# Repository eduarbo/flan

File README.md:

# Flan

**Homemade, like a good flan.** An open-source wireless split keyboard in four sizes, with interchangeable cases, magnetic display frames, 31 themes and your own keycap colors.

**[flankbd.com →](https://flankbd.com/)** · **[Explore and customize in 3D →](https://flankbd.com/explore/)** · **[Parts and buying links →](docs/parts.md)** · **[Order PCBs →](docs/electronics.md#order-the-two-pcbs)** · **[Build guide →](docs/build.md)** · **[Edit in FreeCAD →](docs/freecad.md)**

| [Home page](https://flankbd.com/) | [3D explorer](https://flankbd.com/explore/) |
|---|---|
|  |  |

**[Four sizes](docs/variants.md)** — Flan36 (3 × 5 + 3 per half) is the reference. Flan42 adds the outer pinky column, Flan46 a number row and Flan54 both. Every size keeps the thumbs and the bay, and has routed PCBs, six silkscreen editions, the four case styles and ZMK firmware. Pick one in the explorer under **Design → Size**.

**[Silkscreen editions](docs/electronics.md#editions)** — Asanoha, Kikkō, Sayagata, Seigaiha, Meandro and Vías: six all-over back patterns around the Flan signature, one Gerber package each. Preview them with JLCPCB's seven solder-mask colors under **Design → PCB**, which links the matching ZIPs.

**[Themes and print kits](docs/themes-printing.md)** — Thirty-one coordinated themes, personal keycap palettes, linked rim/frame colors and selected STL/3MF parts.

**[Lower, level stack](docs/level-stack.md)** — The frame and removable switch-covering shell reach 14.50 mm; the glass sits 0.20 mm below them. The display uses its supplied 5 mm socket + 2 mm header; physical assembly remains to be tested.

**[Case styles](docs/cases.md)** — Level, Solid, Color rim and Terrace; actual meshes in the explorer.

**[Using the explorer](docs/viewer.md)** — Design, Parts and Build beside the model (Build lists every part, PCB, print file and firmware for your design), a phone sheet with the home page's tabs, share links that open your exact keyboard, English and Spanish. [Port refinement and verification](docs/reviews/interaction-refinement.md) documents the restored frame wall around USB and power access, including the retained cable and switch clearances.

Flan is a low-profile wireless split keyboard in development by [Eduardo Ruiz](https://github.com/eduarbo). Its original CAD is designed by Eduardo; Flan36 has five columns and three thumb keys per half.

- **KLP Lamé choices:** all 38 Choc-stem variants catalogued; 28 qualify in at least one position. The explorer checks complete combinations and exports a configuration for FreeCAD.
- **Magnetic frames:** six Ø2 × 3 mm base magnets pair with six Ø2 × 4 mm frame magnets from existing stock; [polarity and assembly](docs/build.md#magnetic-frame-and-service). Talavera (default), Game Boy, SNES, 2000s Phone, iPod and Hanafuda. Up to four solid colors in flush inlays, with matching rim and key palettes.
- **Keycap colors:** paint all keys, rows, columns or individual keys; save and share your own palettes.
- **Free tools:** KiCad for electronics, FreeCAD for the case, StepUp for exchange. Editable source, STEP/STL, offline explorer and GLB included.
- **Intended hardware:** Choc v1 hot-swap, two nice!nano controllers and two nice!view displays. One display remains the fallback.

**Status: first Flan36 parts ordered; physical qualification pending.** Both Flan36 PCBs pass DRC, schematic parity and ERC with no unconnected items. Three [ZMK firmware builds](docs/firmware.md) cover two displays or a left-only display. [Prototype fabrication files and verification](docs/electronics.md) are included. Exact connectors, printed retention, BLE, charging and measured power still need hardware tests.

**First build:** [Flan36 purchase sequence and test record](docs/first-build.md). **Introducing Flan:** [copy, images and verified claim boundaries](docs/launch.md).

| Level | Solid | Color rim | Terrace |
|---|---|---|---|
|  |  |  |  |

**[Keycaps and frames](docs/customize.md) · [Design](docs/design.md) · [Build](docs/build.md) · [CAD files](docs/cad.md) · [Explorer](docs/viewer.md) · [Progress](docs/progress.md)**

Flan36 is inspired by [Piantor by beekeeb](https://github.com/beekeeb/piantor) and keeps its 36 key positions and angles; the wireless PCBs, case outline, cases, frames and firmware are original. The viewer uses [KLP Lamé by braindefender](https://github.com/braindefender/KLP-Lame-Keycaps). [Credits and licenses](ATTRIBUTION.md). [Contributing](CONTRIBUTING.md).

## Support Flan

Flan is free to build. If it is useful to you, [support it on Ko-fi](https://ko-fi.com/eduarbo): it funds prototypes, test boards and new sizes.

## License, trademark and official kits

Build, modify, share and sell Flan under [GPL-3.0-or-later](LICENSE), with the third-party terms listed in [ATTRIBUTION.md](ATTRIBUTION.md). The license covers the files, not the **Flan** name and logos: products sold under the Flan name or carrying its marks need permission. Official kits come only from Eduardo or licensed sellers. [Trademark policy and official kits →](TRADEMARKS.md)

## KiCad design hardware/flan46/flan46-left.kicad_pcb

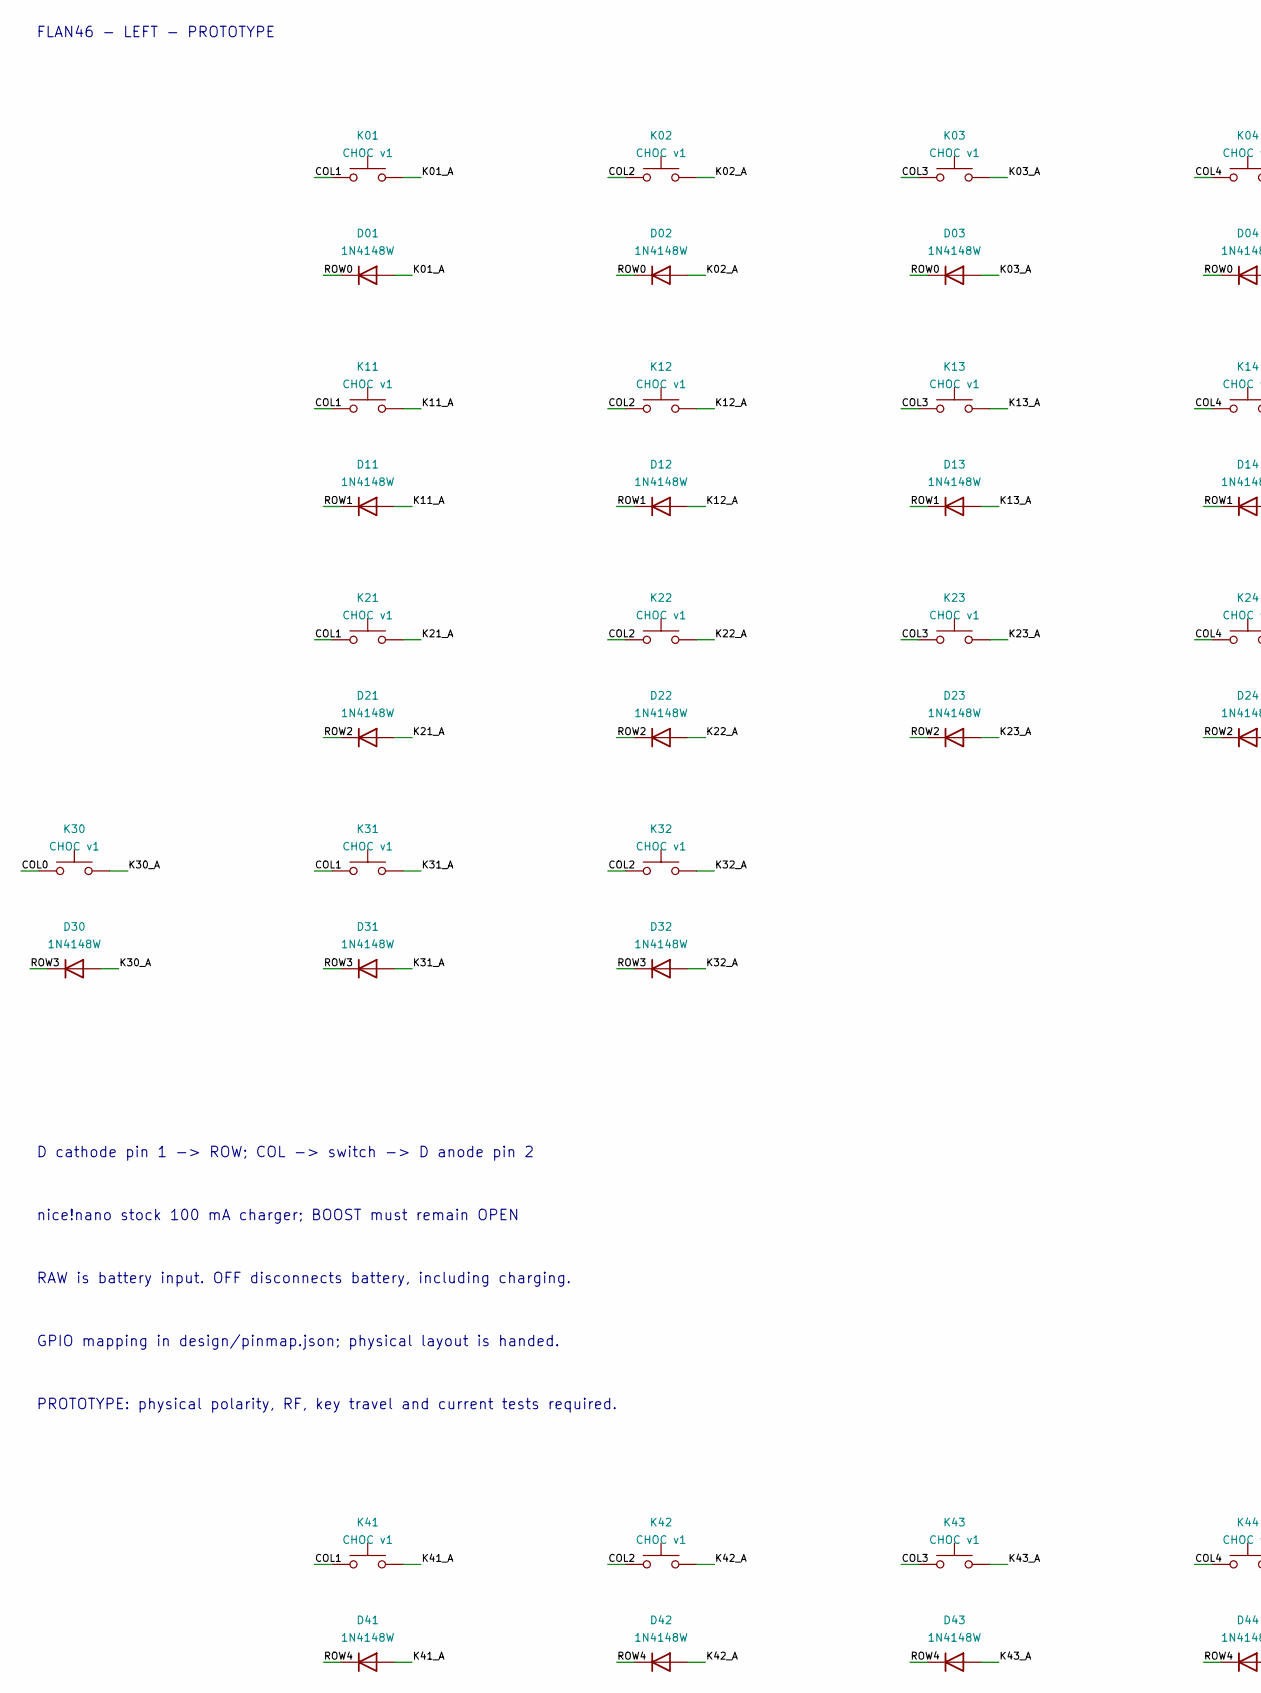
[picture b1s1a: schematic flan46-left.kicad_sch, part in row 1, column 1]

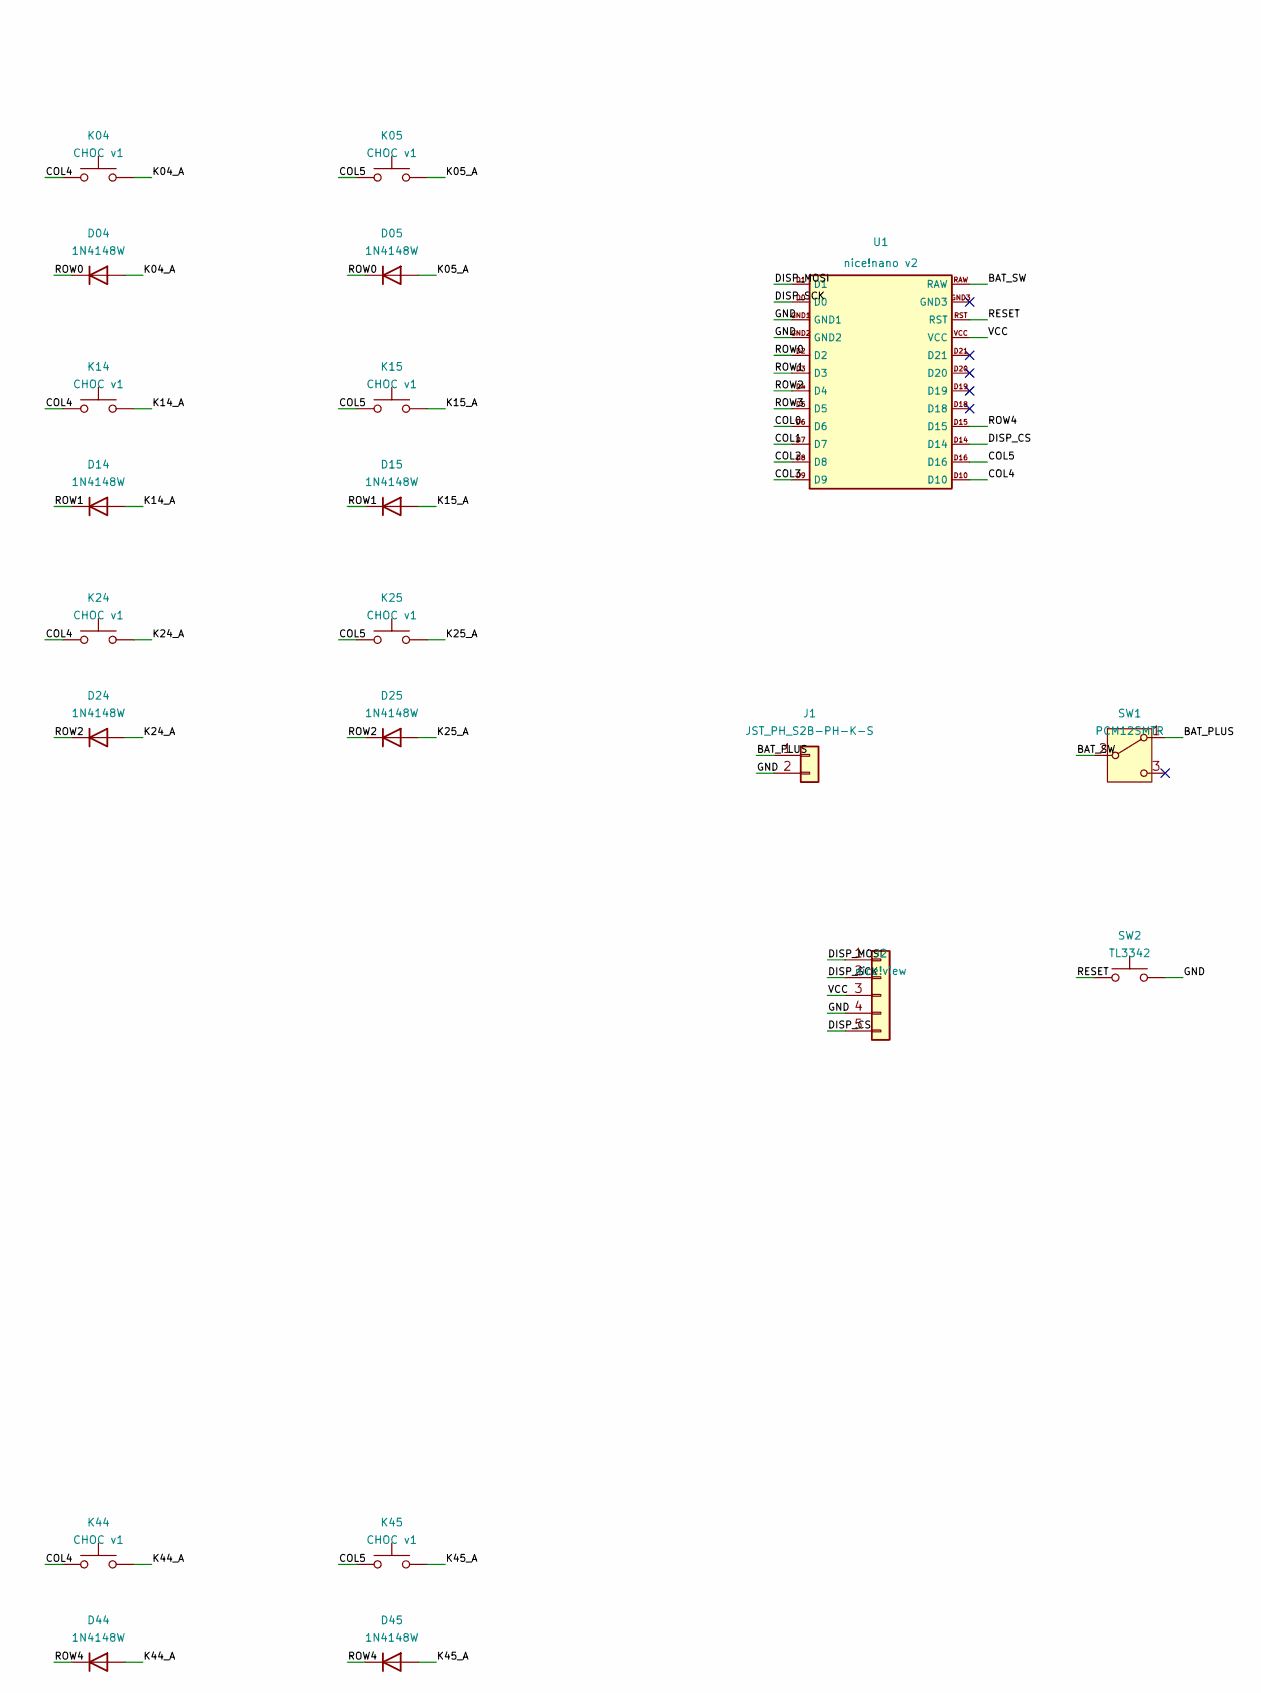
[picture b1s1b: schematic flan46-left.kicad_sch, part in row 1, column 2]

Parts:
D01, D02, D03, D04, D05, D11, D12, D13, D14, D15, D21, D22, D23, D24, D25, D30, D31, D32, D41, D42, D43, D44, D45: 1N4148W; D_SOD-123
J1: JST_PH_S2B-PH-K-S; JST_PH_S2B-PH-K_1x02_P2.00mm_Horizontal
J2: nice!view; nice_view_5pin
K01, K02, K03, K04, K05, K11, K12, K13, K14, K15, K21, K22, K23, K24, K25, K30, K31, K32, K41, K42, K43, K44, K45: CHOC v1; Kailh_socket_PG1350_optional
SW1: PCM12SMTR; SW_SPDT_PCM12
SW2: TL3342; SW_SPST_TL3342
U1: nice!nano v2; nice_nano_v2_standard_edge

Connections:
/BAT_PLUS: J1.1, SW1.1 (A)
/BAT_SW: SW1.2 (B), U1.RAW
/COL0: K30.1, U1.D6
/COL1: K01.1, K11.1, K21.1, K31.1, K41.1, U1.D7
/COL2: K02.1, K12.1, K22.1, K32.1, K42.1, U1.D8
/COL3: K03.1, K13.1, K23.1, K43.1, U1.D9
/COL4: K04.1, K14.1, K24.1, K44.1, U1.D10
/COL5: K05.1, K15.1, K25.1, K45.1, U1.D16
/DISP_CS: J2.5, U1.D14
/DISP_MOSI: J2.1, U1.D1
/DISP_SCK: J2.2, U1.D0
/GND: J1.2, J2.4, SW2.2, U1.GND1, U1.GND2
/K01_A: D01.2 (A), K01.2
/K02_A: D02.2 (A), K02.2
/K03_A: D03.2 (A), K03.2
/K04_A: D04.2 (A), K04.2
/K05_A: D05.2 (A), K05.2
/K11_A: D11.2 (A), K11.2
/K12_A: D12.2 (A), K12.2
/K13_A: D13.2 (A), K13.2
/K14_A: D14.2 (A), K14.2
/K15_A: D15.2 (A), K15.2
/K21_A: D21.2 (A), K21.2
/K22_A: D22.2 (A), K22.2
/K23_A: D23.2 (A), K23.2
/K24_A: D24.2 (A), K24.2
/K25_A: D25.2 (A), K25.2
/K30_A: D30.2 (A), K30.2
/K31_A: D31.2 (A), K31.2
/K32_A: D32.2 (A), K32.2
/K41_A: D41.2 (A), K41.2
/K42_A: D42.2 (A), K42.2
/K43_A: D43.2 (A), K43.2
/K44_A: D44.2 (A), K44.2
/K45_A: D45.2 (A), K45.2
/RESET: SW2.1, U1.RST
/ROW0: D01.1 (K), D02.1 (K), D03.1 (K), D04.1 (K), D05.1 (K), U1.D2
/ROW1: D11.1 (K), D12.1 (K), D13.1 (K), D14.1 (K), D15.1 (K), U1.D3
/ROW2: D21.1 (K), D22.1 (K), D23.1 (K), D24.1 (K), D25.1 (K), U1.D4
/ROW3: D30.1 (K), D31.1 (K), D32.1 (K), U1.D5
/ROW4: D41.1 (K), D42.1 (K), D43.1 (K), D44.1 (K), D45.1 (K), U1.D15
/VCC: J2.3, U1.VCC

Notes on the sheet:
FLAN46 - LEFT - PROTOTYPE
D cathode pin 1 -> ROW; COL -> switch -> D anode pin 2
nice!nano stock 100 mA charger; BOOST must remain OPEN
RAW is battery input. OFF disconnects battery, including charging.
GPIO mapping in design/pinmap.json; physical layout is handed.
PROTOTYPE: physical polarity, RF, key travel and current tests required.

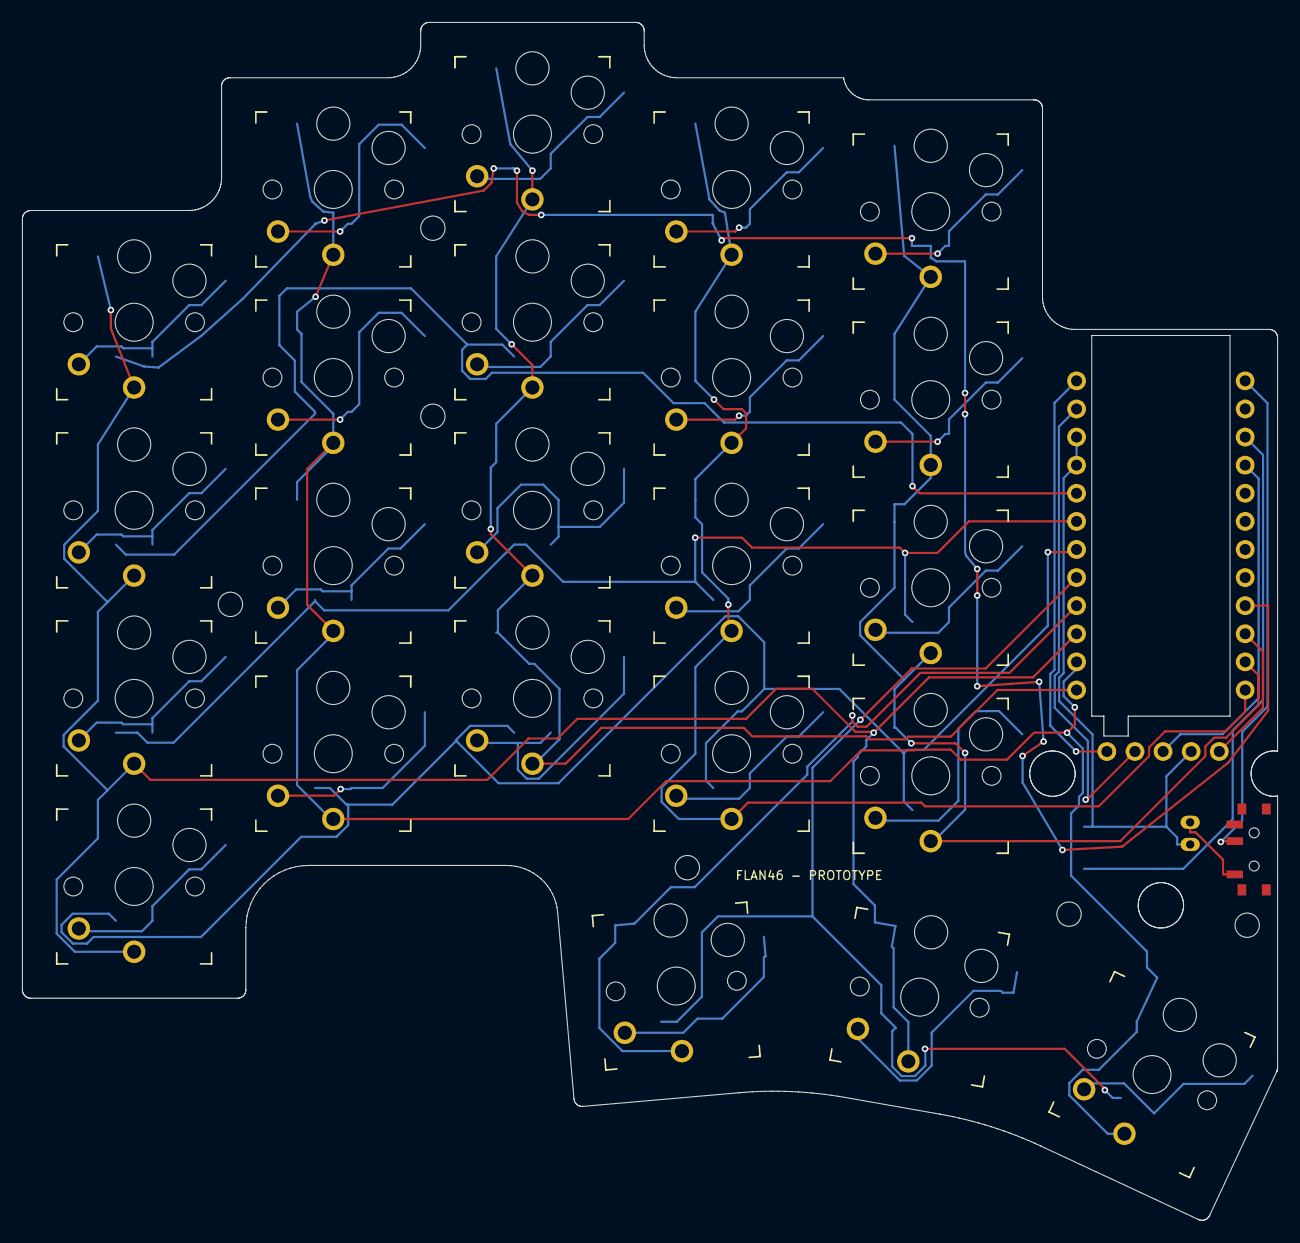
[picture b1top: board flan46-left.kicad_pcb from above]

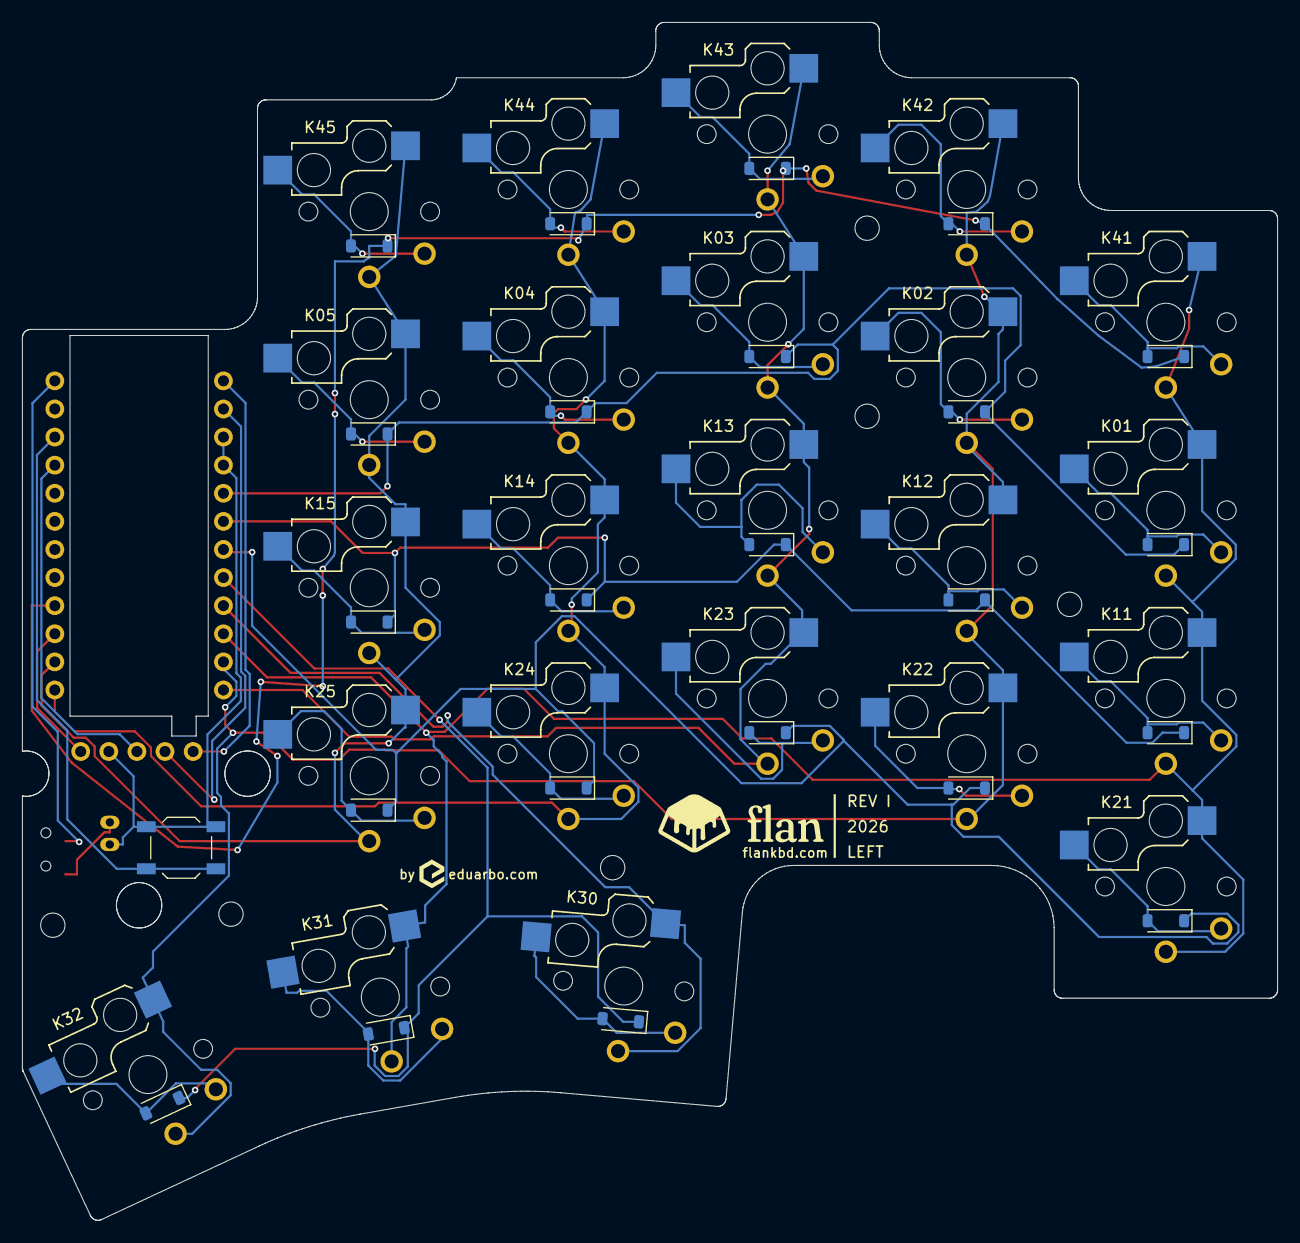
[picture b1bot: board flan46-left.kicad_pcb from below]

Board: 2 copper layers, 113.4 x 108.3 mm, 57 parts (24 on the bottom side), 42 nets.

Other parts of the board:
H1, H2, H3, H4, H5, H7: MountingHole_2.2mm_M2

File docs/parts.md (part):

# Parts and buying guide

**Use [Build in the explorer](https://flankbd.com/explore/) for your configuration’s itemized list, supplier links, quantities and CSV export.** The reference below documents the component selections.

**One complete split keyboard. Quantities cover both halves of Flan36; [other sizes](#quantities-by-size) change only the per-key parts and a few screws.**

This is the selected purchasing BOM for the routed revI prototype, an original design by Eduardo Ruiz. The display uses the connector supplied with nice!view; the controller sockets and pins are specified below. **Physical assembly has not been qualified:** supplied-part tolerances, printed fit, magnetic retention and electrical operation still need the [build checks](build.md).

[Custom PCBs](electronics.md) · [Quantities by size](#quantities-by-size) · [Typeractive shopping list](#typeractive-shopping-list) · [Controllers](#controllers) · [Displays](#displays) · [Switches](#switches-and-hot-swap) · [Battery](#battery) · [Connectors](#removable-connectors) · [Small parts](#small-electrical-parts) · [Printed parts](#printed-parts)

**First prototype:** follow the [Flan36 purchase sequence and test record](first-build.md). [Current supply check](#supply-check-2026-10-20).

**Custom PCBs: 1 left + 1 right**, two layers, 1.6 mm FR4, nominal 1 oz copper. Download the [left fabrication ZIP](https://raw.githubusercontent.com/eduarbo/flan/main/hardware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 and [right fabrication ZIP](https://raw.githubusercontent.com/eduarbo/flan/main/hardware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, then follow the [ordering settings](electronics.md#order-the-two-pcbs). The supplied pin maps differ between halves; neither board is interchangeable with Piantor or the historical placement studies.

## Quantities by size

Everything not listed here is the same for every size: two controllers, two displays, two batteries, two power switches, two reset buttons, the controller connectors, magnets, feet, cable and tape. Packs of switches, sockets and diodes come in tens; each count keeps at least four spares.

| | Flan36 | Flan42 | Flan46 | Flan54 |
|---|:-:|:-:|:-:|:-:|
| Keys per half | 3 × 5 + 3 | 3 × 6 + 3 | 4 × 5 + 3 | 4 × 6 + 3 |
| Choc v1 switches | 36 · **4 packs** | 42 · **5 packs** | 46 · **5 packs** | 54 · **6 packs** |
| Choc hot-swap sockets | 36 · **4 packs** | 42 · **5 packs** | 46 · **5 packs** | 54 · **6 packs** |
| 1N4148W diodes | 36 · **4 packs** | 42 · **5 packs** | 46 · **5 packs** | 54 · **6 packs** |
| KLP Lamé keycaps (printed) | 36 | 42 | 46 | 54 |
| M2 × 6 screws | 6 | 8 | 8 | 12 |
| M2 × 4 screws | 4 | 4 | 4 | 4 |
| Printed spacers/washers | 6 | 8 | 8 | 12 |
| PCB fabrication ZIPs | [left](https://raw.githubusercontent.com/eduarbo/flan/main/hardware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 · [right](https://raw.githubusercontent.com/eduarbo/flan/main/hardware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 | [left](https://raw.githubusercontent.com/eduarbo/flan/main/hardware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 · [right](https://raw.githubusercontent.com/eduarbo/flan/main/hardware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 | [left](https://raw.githubusercontent.com/eduarbo/flan/main/hardware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 · [right](https://raw.githubusercontent.com/eduarbo/flan/main/hardware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 | [left](https://raw.githubusercontent.com/eduarbo/flan/main/hardware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 · [right](https://raw.githubusercontent.com/eduarbo/flan/main/hardware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 |

Every key has its own diode. The added fasteners (H6 on Flan42, H7 on Flan46, H6–H8 on Flan54, per half) copy H1 or H2, so they take M2 × 6 screws and a printed washer. The other sizes are built digitally only; Flan36 is the reference for a first build. [The Flan family](variants.md)

## Typeractive shopping list

| Item | Quantity / store selection | Assembly note |
|---|---|---|
| [nice!nano v2](https://typeractive.xyz/products/nice-nano) | **2 units** | Install with the specified Mill-Max sockets/pins at Z8.20 mm |
| [nice!view](https://typeractive.xyz/products/nice-view) | **2 units** | Use each display's supplied 5-pin socket and header; 7.00 mm board separation |
| [Choc v1 switches](https://typeractive.xyz/products/choc-switches) | **4 packs of 10**; Pro Red baseline | 36 required, 4 spares |
| [Kailh hot-swap sockets](https://typeractive.xyz/products/hotswap-sockets) | **4 packs of 10; select Choc** | Do not select MX |
| [1N4148W SMD diodes](https://typeractive.xyz/products/smd-diodes) | **4 packs of 10** | SOD-123 family; verify supplied marking/footprint |
| [Battery jack](https://typeractive.xyz/products/battery-jack) | **1 pack of 2; white** | JST S2B-PH-K-S side-entry reference; 2 mm nominal footprint |

No additional display connector pack is needed. The selected controller connectors, battery, power switch and reset button are in the following list; the similarly named Typeractive alternatives are not the selected parts.

## DigiKey shopping list

| Item | Quantity | Selection |
|---|---:|---|
| [Adafruit 1570](https://www.digikey.com/en/products/detail/adafruit-industri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 | **2** | Protected 1S 100 mAh LiPo; keep the nice!nano BOOST jumper open |
| [C&K PCM12SMTR](https://www.digikey.com/en/products/detail/c-k/PCM12SMTR/1640112) | **2** | Exact power-switch reference; cut tape |
| [E-Switch TL3342F160QG/TR](https://www.digikey.com/en/products/detail/e-switch/TL3342F1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 | **2** | Exact reset-button reference; cut tape |
| [Mill-Max 315-43-164-41-003000](https://www.digikey.com/en/products/detail/mill-max-manufact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 | **1 strip of 64** | Cut four 12-contact strips, using sacrificial contacts at the cuts |
| [Mill-Max 3320-0-00-15-00-00-03-0](https://www.digikey.com/en/products/detail/mill-max-manufact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 | **50** | Round pins; 48 used, 2 spares |
| [Essentra RBS-5BK](https://www.digikey.com/en/products/detail/essentra-componen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 | **8** | Adhesive feet, Ø12.7 × 1.6 mm; DigiKey RPC1381-ND |
| [Adafruit 4199](https://www.digikey.com/en/products/detail/adafruit-industri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 | **1** | USB-C to USB-C data cable, 1 m; DigiKey 1528-4199-ND; $9.95 when checked |
| [Olimex KAPTON-TAPE10MM](https://www.digikey.com/en/products/detail/olimex-ltd/KAPTON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 | **1 roll** | Insulating tape, 10 mm × 30 m; DigiKey 1188-KAPTON-TAPE10MM-ND; $2.88 when checked |

The 64-position strip replaces the unavailable 12-position version in the same 315 family and suffix. The PCM12SMTR is obsolete but was stocked when this list was checked; a different switch requires a footprint check. Prices and availability were checked on October 10, 2026 and can change at checkout. Lithium batteries require an eligible US ground service; do not select an air or prohibited postal service. Custom PCBs and printed parts are separate.

## Supply check 2026-10-20

Observed catalog availability is a snapshot, not a reservation or a delivery promise. Recheck the exact selection and final shipping/tax total at checkout.

| Supplier / line | Observed result |
|---|---|
| Typeractive: nice!nano v2, nice!view, Pro Red, Choc sockets, diodes, white battery jack | All selected variants marked available in the supplier's product data. Two controllers, two displays, four packs each of switches/sockets/diodes and one jack pack: **US$128** before shipping/tax. Product links are above. |
| DigiKey: Adafruit 1570, PCM12SMTR, TL3342F160QG/TR, 315-43-164-41-003000, 3320-0-00-15-00-00-03-0 | All five selected lines listed in stock. The PCM12SMTR remains obsolete; do not treat its remaining inventory as a production supply plan. Exact product links are above. |
| [NBK SLH-M2-6](https://www.nbk1560.com/en-US/products/specialscrew/nedzicom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 | Exact low-head reference: Ø3.8 × 1.3 mm head, M2 × 6. Catalog pack of **50**, US$27.54; six used. Dispatch availability not verified. |
| [NBK SSH-M2-4](https://www.nbk1560.com/en-US/products/specialscrew/nedzicom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 | Exact ultra-low-head reference: Ø4 × 1.1 mm head, M2 × 4. Catalog pack of **10**, US$15.91; four used. Dispatch availability not verified. |

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
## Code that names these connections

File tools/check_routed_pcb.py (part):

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            assert expected[ref, "1"] == f'/COL{key["col"]}'
            assert expected[ref, "2"] == expected[diode, "2"] == f"/{ref}_A"
            assert expected[diode, "1"] == f'/ROW{key["row"]}'
        pins = {"D0": "DISP_SCK", "D1": "DISP_MOSI", "D14": "DISP_CS", "RAW": "BAT_SW", "VCC": "VCC", "RST": "RESET"}
        pins.update({f"D{x}": f"ROW{i}" for i, x in enumerate(pinmap[side]["rows"])})
        pins.update({f"D{x}": f"COL{i}" for i, x in enumerate(pinmap[side]["cols"])})
        if family and variant in pinmap_variants:   # the number row's ROW4 pin, and GND3 released on the left
            from build_variant_pcb import RELEASE
            pins[f'D{pinmap_variants[variant][side]["row4"]}'] = "ROW4"
            if side in RELEASE:
                assert expected["U1", RELEASE[side]].startswith("unconnected-"), (side, RELEASE[side])
            # without U1 GND3 on the left, J1's GND and every GND pad must still be one copper net
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

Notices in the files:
docs/parts.md:
they are not relicensed under this repository’s license. They need internet access and are not bundled in the offline 3D viewer. Flan36 renders have separate [attribution](../ATTRIBUTION.md).
tools/check_routed_pcb.py:
Run with KiCad Python. SPDX-License-Identifier: GPL-3.0-or-later
